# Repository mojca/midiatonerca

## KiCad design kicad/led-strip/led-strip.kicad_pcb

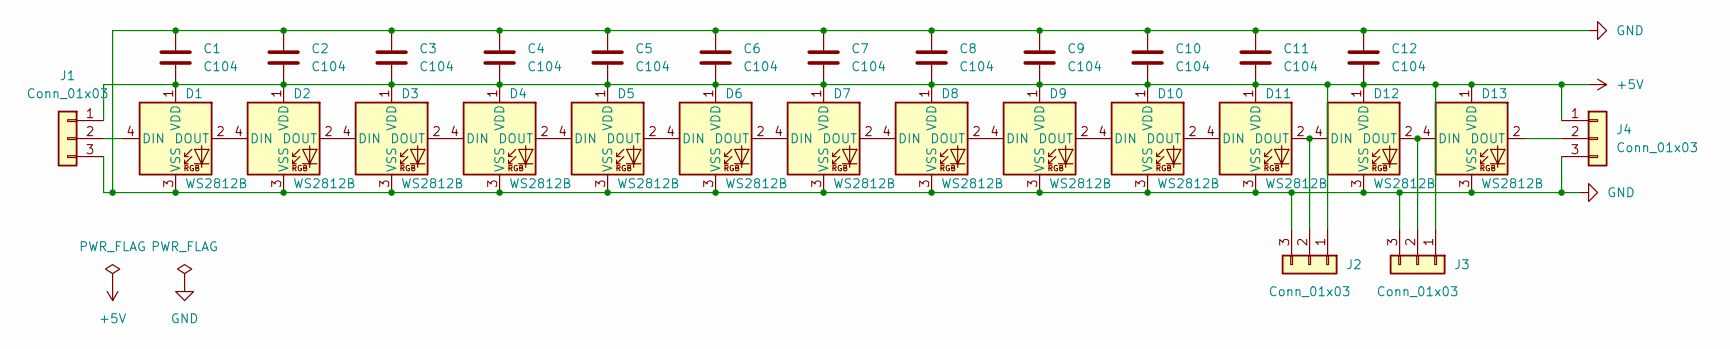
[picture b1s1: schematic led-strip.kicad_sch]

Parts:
C1, C2, C3, C4, C5, C6, C7, C8, C9, C10, C11, C12: C104; C_1206_3216Metric_Pad1.33x1.80mm_HandSolder; LCSC Part # C24497
D1, D2, D3, D4, D5, D6, D7, D8, D9, D10, D11, D12, D13: WS2812B; LED_WS2812B_PLCC4_5.0x5.0mm_P3.2mm; LCSC Part # C2761795
J1, J2, J3, J4: Conn_01x03; SolderWirePad_1x03_SMD_1x3mm

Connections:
+5V: C1.2, C2.2, C3.2, C4.2, C5.2, C6.2, C7.2, C8.2, C9.2, C10.2, C11.2, C12.2, D1.1 (VDD), D2.1 (VDD), D3.1 (VDD), D4.1 (VDD), D5.1 (VDD), D6.1 (VDD), D7.1 (VDD), D8.1 (VDD), D9.1 (VDD), D10.1 (VDD), D11.1 (VDD), D12.1 (VDD), D13.1 (VDD), J1.1, J2.1, J3.1, J4.1
GND: C1.1, C2.1, C3.1, C4.1, C5.1, C6.1, C7.1, C8.1, C9.1, C10.1, C11.1, C12.1, D1.3 (VSS), D2.3 (VSS), D3.3 (VSS), D4.3 (VSS), D5.3 (VSS), D6.3 (VSS), D7.3 (VSS), D8.3 (VSS), D9.3 (VSS), D10.3 (VSS), D11.3 (VSS), D12.3 (VSS), D13.3 (VSS), J1.3, J2.3, J3.3, J4.3
unnamed: D1.2 (DOUT), D2.4 (DIN)
unnamed: D1.4 (DIN), J1.2
unnamed: D2.2 (DOUT), D3.4 (DIN)
unnamed: D3.2 (DOUT), D4.4 (DIN)
unnamed: D4.2 (DOUT), D5.4 (DIN)
unnamed: D5.2 (DOUT), D6.4 (DIN)
unnamed: D6.2 (DOUT), D7.4 (DIN)
unnamed: D7.2 (DOUT), D8.4 (DIN)
unnamed: D8.2 (DOUT), D9.4 (DIN)
unnamed: D10.2 (DOUT), D11.4 (DIN)
unnamed: D9.2 (DOUT), D10.4 (DIN)
unnamed: D11.2 (DOUT), D12.4 (DIN), J2.2
unnamed: D12.2 (DOUT), D13.4 (DIN), J3.2
unnamed: D13.2 (DOUT), J4.2

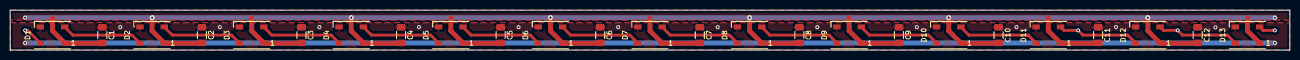
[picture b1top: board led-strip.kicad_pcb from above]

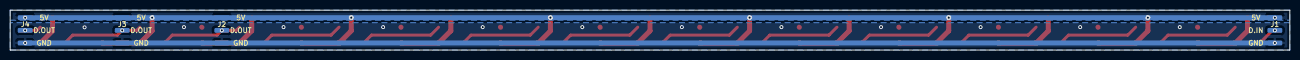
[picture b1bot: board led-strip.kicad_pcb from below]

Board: 2 copper layers, 257.0 x 8.0 mm, 29 parts (4 on the bottom side), 16 nets.

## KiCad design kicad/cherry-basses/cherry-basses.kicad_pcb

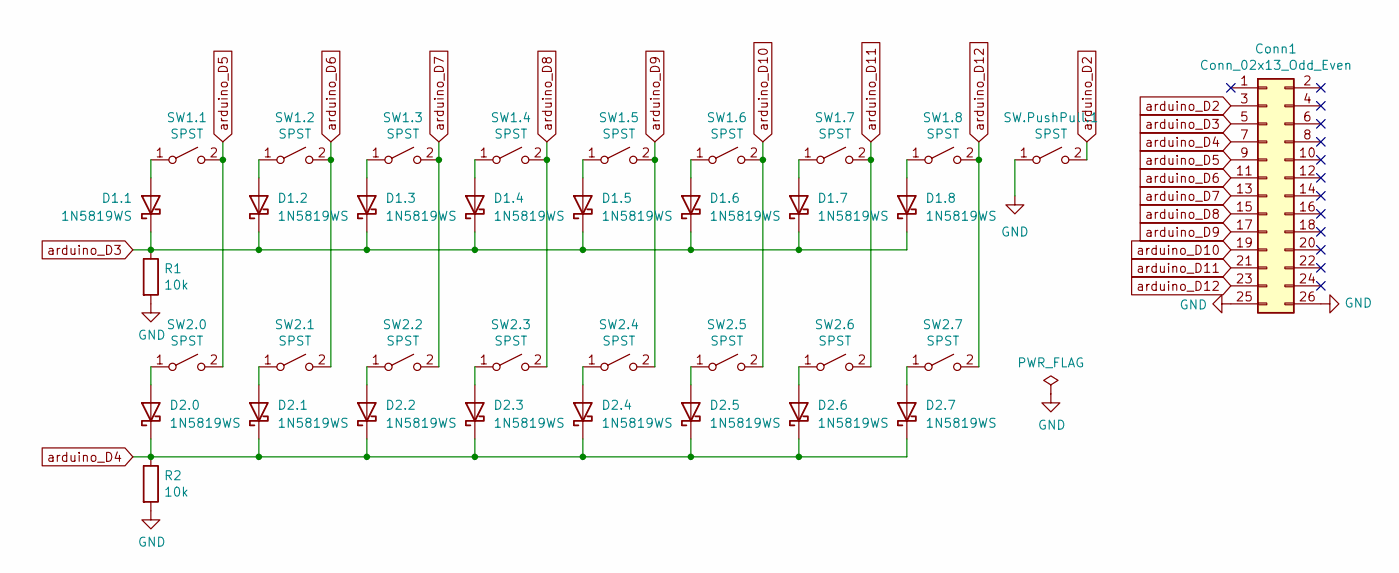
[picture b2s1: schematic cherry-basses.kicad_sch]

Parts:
Conn1: Conn_02x13_Odd_Even; IDC-Header_2x13_P2.54mm_Vertical; LCSC Part # C692426
D1.1, D1.2, D1.3, D1.4, D1.5, D1.6, D1.7, D1.8, D2.0, D2.1, D2.2, D2.3, D2.4, D2.5, D2.6, D2.7: 1N5819WS; D_SOD-323_HandSoldering; LCSC Part # C191023
R1, R2: 10k; R_1206_3216Metric_Pad1.30x1.75mm_HandSolder; LCSC Part # C17902
SW1.1, SW1.2, SW1.3, SW1.4, SW1.5, SW1.6, SW1.7, SW1.8, SW2.0, SW2.1, SW2.2, SW2.3, SW2.4, SW2.5, SW2.6, SW2.7: SPST; SW_Cherry_MX_1.00u_PCB
SW.PushPull.1: SPST; Molex_KK-254_AE-6410-02A_1x02_P2.54mm_Vertical

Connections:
GND: Conn1.25, Conn1.26, R1.2, R2.2, SW.PushPull.1.1 (A)
unnamed: D1.1.2 (A), SW1.1.1 (A)
unnamed: D1.2.2 (A), SW1.2.1 (A)
unnamed: D1.3.2 (A), SW1.3.1 (A)
unnamed: D1.4.2 (A), SW1.4.1 (A)
unnamed: D1.5.2 (A), SW1.5.1 (A)
unnamed: D1.6.2 (A), SW1.6.1 (A)
unnamed: D1.7.2 (A), SW1.7.1 (A)
unnamed: D1.8.2 (A), SW1.8.1 (A)
unnamed: D2.0.2 (A), SW2.0.1 (A)
unnamed: D2.1.2 (A), SW2.1.1 (A)
unnamed: D2.2.2 (A), SW2.2.1 (A)
unnamed: D2.3.2 (A), SW2.3.1 (A)
unnamed: D2.4.2 (A), SW2.4.1 (A)
unnamed: D2.5.2 (A), SW2.5.1 (A)
unnamed: D2.6.2 (A), SW2.6.1 (A)
unnamed: D2.7.2 (A), SW2.7.1 (A)
arduino_D2: Conn1.3, SW.PushPull.1.2 (B)
arduino_D3: Conn1.5, D1.1.1 (K), D1.2.1 (K), D1.3.1 (K), D1.4.1 (K), D1.5.1 (K), D1.6.1 (K), D1.7.1 (K), D1.8.1 (K), R1.1
arduino_D4: Conn1.7, D2.0.1 (K), D2.1.1 (K), D2.2.1 (K), D2.3.1 (K), D2.4.1 (K), D2.5.1 (K), D2.6.1 (K), D2.7.1 (K), R2.1
arduino_D5: Conn1.9, SW1.1.2 (B), SW2.0.2 (B)
arduino_D6: Conn1.11, SW1.2.2 (B), SW2.1.2 (B)
arduino_D7: Conn1.13, SW1.3.2 (B), SW2.2.2 (B)
arduino_D8: Conn1.15, SW1.4.2 (B), SW2.3.2 (B)
arduino_D9: Conn1.17, SW1.5.2 (B), SW2.4.2 (B)
arduino_D10: Conn1.19, SW1.6.2 (B), SW2.5.2 (B)
arduino_D11: Conn1.21, SW1.7.2 (B), SW2.6.2 (B)
arduino_D12: Conn1.23, SW1.8.2 (B), SW2.7.2 (B)

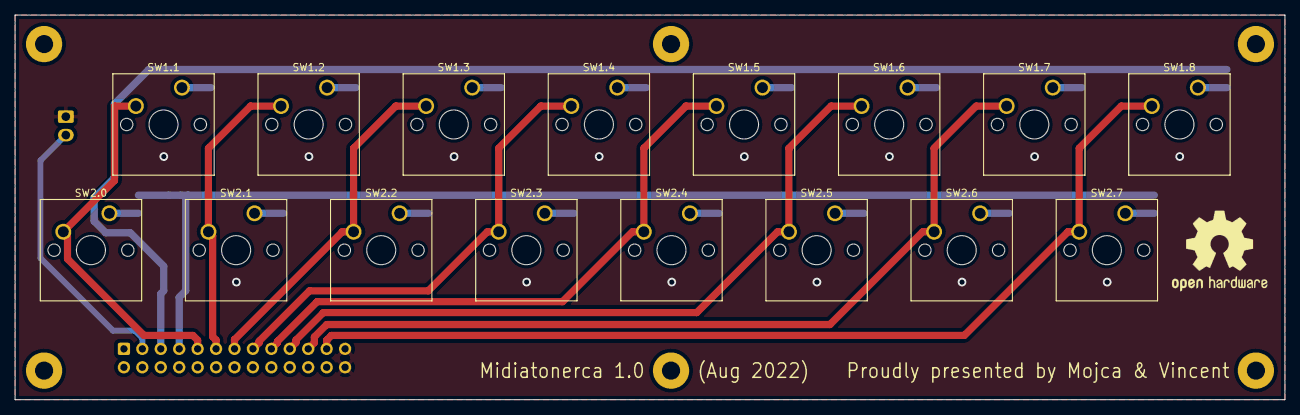
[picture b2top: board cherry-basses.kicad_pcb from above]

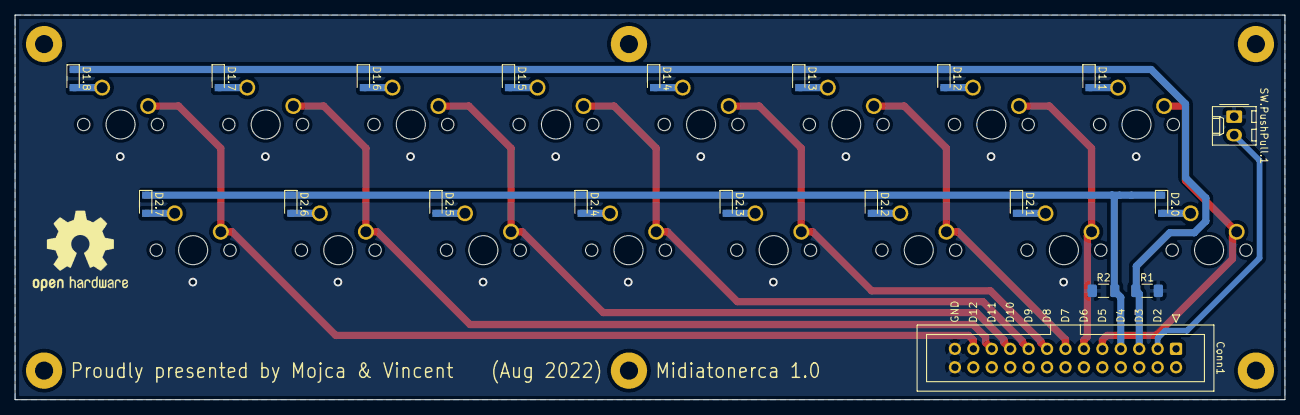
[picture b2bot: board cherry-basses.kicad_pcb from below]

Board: 2 copper layers, 175.0 x 53.0 mm, 36 parts (20 on the bottom side), 28 nets.

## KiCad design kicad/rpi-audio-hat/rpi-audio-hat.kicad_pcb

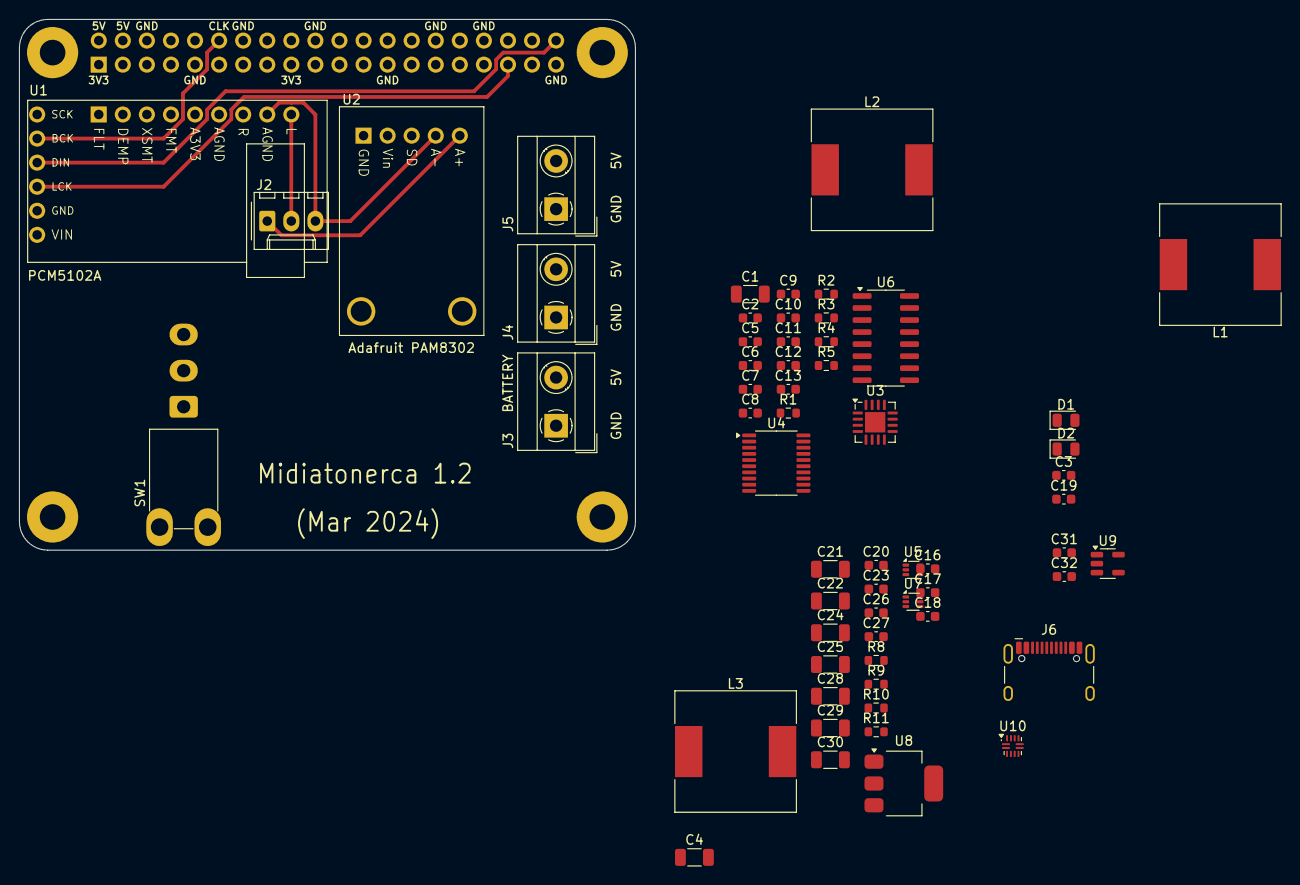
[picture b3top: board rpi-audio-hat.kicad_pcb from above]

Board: 4 copper layers, 65.0 x 56.0 mm, 61 parts (1 on the bottom side), 46 nets.

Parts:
C1, C4, C21, C22, C24, C25, C28, C29, C30: 22uF; C_1206_3216Metric
C2, C3, C6, C7, C9, C13, C19, C20, C26: 100nF; C_0603_1608Metric
C5, C8, C10, C11, C12, C18, C31, C32: 10uF; C_0603_1608Metric
C16, C17: 1uF; C_0603_1608Metric
C23, C27: 22pF; C_0603_1608Metric
D1: Green; LED_0805_2012Metric
D2: Red; LED_0805_2012Metric
J1: Raspberry_Pi_2_3; PinSocket_2x20_P2.54mm_Vertical
J2: Conn_Volume_Slider; Molex_KK-254_AE-6410-03A_1x03_P2.54mm_Vertical
J3, J4, J5: Screw_Terminal_01x02; TerminalBlock_MetzConnect_Type101_RT01602HBWC_1x02_P5.08mm_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
J6: USB_C_Receptacle_USB2.0; USB_C_Receptacle_HCTL_HC-TYPE-C-16P-01A
L1, L2, L3: 3A+ 2.2uH; L_SXN_SMDRI124
R1: 3.9k; R_0603_1608Metric
R2, R3: 220R; R_0603_1608Metric
R4, R5: 100k; R_0603_1608Metric
R8, R10: 220k; R_0603_1608Metric
R9: 30k; R_0603_1608Metric
R11: 22k; R_0603_1608Metric
SW1: SW_SPDT; SW_3P_Mini_Toggle_B068BW_SPDT
U1: PCM5102_breakout
U2: PAM8302A_Adafruit_Board; PAM8302
U3: SLM6800; QFN-16-1EP_4x4mm_P0.65mm_EP2.15x2.15mm
U4: PCM5102A; TSSOP-20_4.4x6.5mm_P0.65mm
U5, U7: TPS563203; SOT-563
U6: PAM8406D; SOP-16_3.9x9.9mm_P1.27mm
U8: TLV76150DCYR; SOT-223-3_TabPin2
U9: LP2985-3.3; SOT-23-5
U10: FUSB303BTMX; Texas_X2QFN-12_1.6x1.6mm_P0.4mm

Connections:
+3.3V: J1.1 (3V3), J1.17 (3V3)
+3.3VA: C5.1, C6.1, C7.1, U4.1 (CPVDD), U4.8 (AVDD), U4.17 (XSMT)
+3V3: C8.1, C9.1, R2.1, R3.1, U4.20 (DVDD)
+5V: C21.1, C23.1, C24.1, J1.2 (5V), J1.4 (5V), J4.2, J5.2, L2.2, R4.1, R8.1, SW1.3 (C), U1.15 (VIN), U2.2 (VDD)
+5VA: C30.1, C31.1, U6.4 (PVDDL), U6.5 (~MUTE), U6.6 (VDD), U6.9 (MODE), U6.12 (~SHND), U6.13 (PVDDR), U8.3 (OUT), U9.1 (VIN), U9.3 (ON/~OFF)
+5VP: J3.2, SW1.2 (B)
+6.6V: C27.1, C28.1, L3.2, R10.1
+VBAT: C22.1, C25.1, U3.9 (BAT), U5.1 (VIN), U5.5 (EN), U7.1 (VIN), U7.5 (EN)
/Battery charger/5VIn: C1.1, C2.1, L1.1, U3.2 (VIN), U3.16 (EN)
/Battery charger/USB-D+: J6.A6 (D+), J6.B6 (D+)
/Battery charger/USB-D-: J6.A7 (D-), J6.B7 (D-)
A+: J2.2, U1.9 (OUTL)
A-: J2.3, U1.8 (AGNDL), U2.4 (IN-)
GND: C1.2, C2.2, C4.2, C5.2, C6.2, C7.2, C8.2, C9.2, C10.2, C12.2, C13.2, C18.2, C19.2, C21.2, C22.2, C24.2, C25.2, C28.2, C29.2, C30.2, C31.2, C32.2, J1.6 (GND), J1.9 (GND), J1.14 (GND), J1.20 (GND), J1.25 (GND), J1.30 (GND), J1.34 (GND), J1.39 (GND), J3.1, J4.1, J5.1, J6.A1 (GND), J6.A12 (GND), J6.B1 (GND), J6.B12 (GND), J6.S1 (SHIELD), R1.2, R5.2, R9.2, R11.2, U1.10 (SCK), U1.14 (GND), U2.1 (GND), U3.4 (PGND), U3.15 (SGND), U3.17 (PGND), U4.3 (CPGND), U4.9 (AGND), U4.10 (DEMP), U4.11 (FLT), U4.16 (FMT), U4.19 (DGND), U5.3 (GND), U6.2 (PGNDL), U6.11 (GND), U6.15 (PGNDR), U7.3 (GND), U8.2 (GND), U9.2 (GND), U10.10 (GND)
unnamed: C3.1, L1.2, U3.5 (LX), U3.6 (LX)
unnamed: C4.1, U3.7 (VSYS), U3.8 (VSYS)
unnamed: D1.2 (A), R2.2
unnamed: D1.1 (K), U3.13 (~CHRG)
unnamed: D2.2 (A), R3.2
unnamed: D2.1 (K), U3.14 (~STBY)
unnamed: J6.A5 (CC1), U10.1 (CC1)
unnamed: J6.B5 (CC2), U10.2 (CC2)
unnamed: C3.2, U3.3 (BST)
unnamed: R1.1, U3.11 (ISET)
unnamed: R4.2, R5.1, U3.1 (NTC)
unnamed: C19.1, U3.12 (TM)
unnamed: C11.2, U4.4 (CAPM)
unnamed: C11.1, U4.2 (CAPP)
unnamed: C12.1, C13.1, U4.18 (LDOO)
unnamed: C10.1, U4.5 (VNEG)
unnamed: C26.2, U5.4 (BST)
unnamed: C27.2, R10.2, R11.1, U5.6 (FB)
unnamed: C26.1, L3.1, U5.2 (SW)
unnamed: C16.2, U6.7 (INL)
unnamed: C17.2, U6.10 (INR)
unnamed: C18.1, U6.8 (VREF)
unnamed: C20.2, U7.4 (BST)
unnamed: C23.2, R8.2, R9.1, U7.6 (FB)
unnamed: C20.1, L2.1, U7.2 (SW)
unnamed: C29.1, U8.1 (IN)
unnamed: C32.1, U9.5 (VOUT)
VUSB: J6.A4 (VBUS), J6.A9 (VBUS), J6.B4 (VBUS), J6.B9 (VBUS), U10.4 (VBUS_DET)
Volume A+: J2.1, U2.5 (IN+)
rpi12: J1.12 (GPIO18/PWM0), U1.11 (BCK), U4.13 (BCK)
rpi35: J1.35 (GPIO19/MISO1), U1.13 (LRCK), U4.12 (SCK), U4.15 (LRCK)
rpi40: J1.40 (GPIO21/SCLK1), U1.12 (DIN), U4.14 (DIN)

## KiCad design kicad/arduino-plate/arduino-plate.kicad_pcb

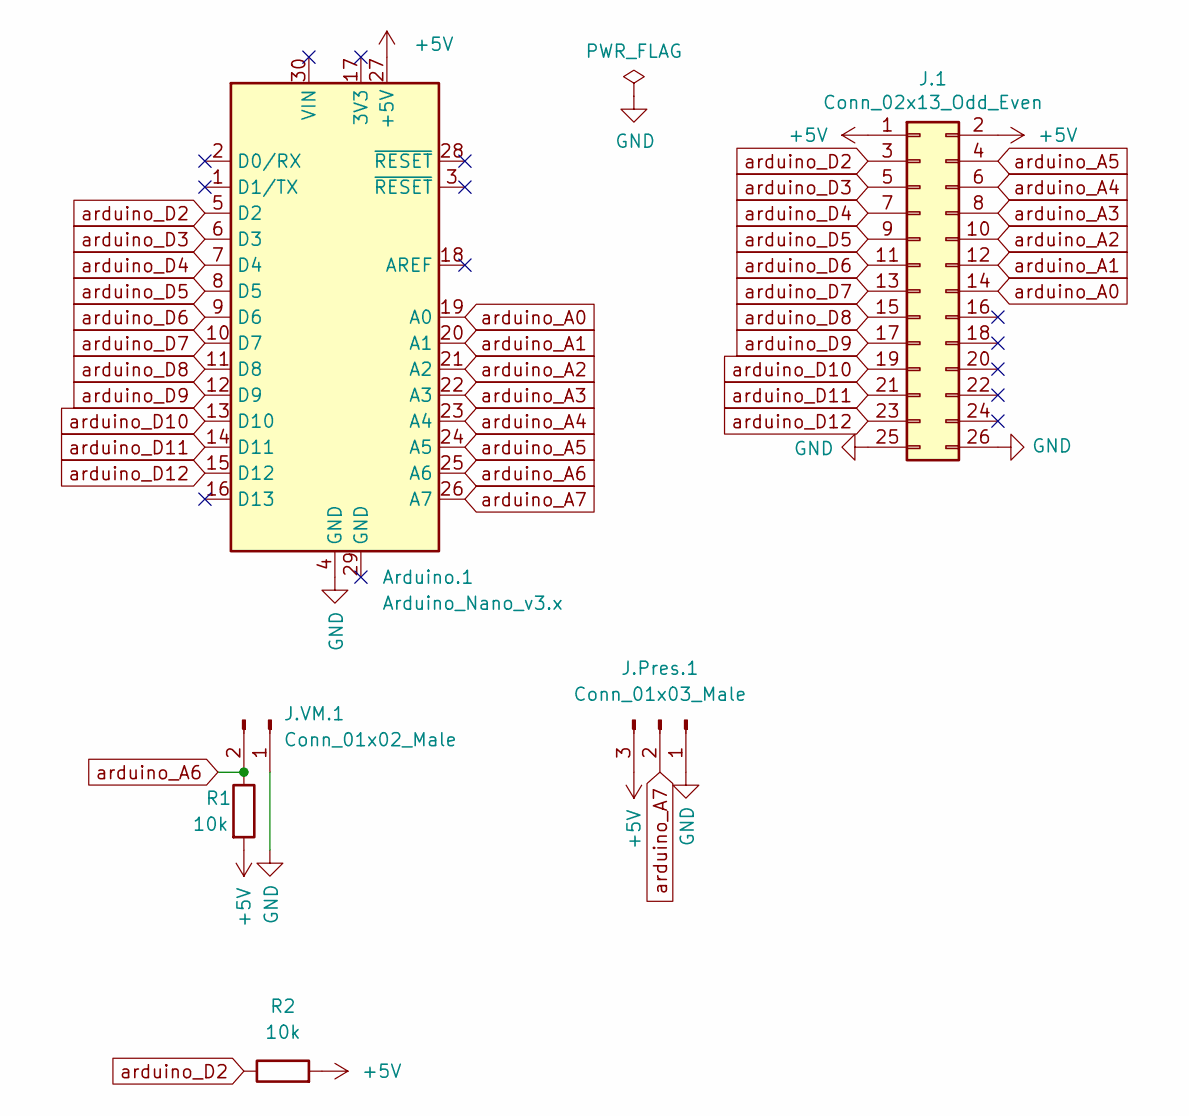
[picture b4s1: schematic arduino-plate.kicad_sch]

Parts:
Arduino.1: Arduino_Nano_v3.x; Arduino_Nano
J.1: Conn_02x13_Odd_Even; IDC-Header_2x13_P2.54mm_Vertical
J.Pres.1: Conn_01x03_Male; Molex_KK-254_AE-6410-03A_1x03_P2.54mm_Vertical
J.VM.1: Conn_01x02_Male; Molex_KK-254_AE-6410-02A_1x02_P2.54mm_Vertical
R1, R2: 10k; R_1206_3216Metric_Pad1.30x1.75mm_HandSolder

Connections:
+5V: Arduino.1.27 (+5V), J.1.1, J.1.2, J.Pres.1.3, R1.2, R2.2
GND: Arduino.1.4 (GND), J.1.25, J.1.26, J.Pres.1.1, J.VM.1.1
arduino_A0: Arduino.1.19 (A0), J.1.14
arduino_A1: Arduino.1.20 (A1), J.1.12
arduino_A2: Arduino.1.21 (A2), J.1.10
arduino_A3: Arduino.1.22 (A3), J.1.8
arduino_A4: Arduino.1.23 (A4), J.1.6
arduino_A5: Arduino.1.24 (A5), J.1.4
arduino_A6: Arduino.1.25 (A6), J.VM.1.2, R1.1
arduino_A7: Arduino.1.26 (A7), J.Pres.1.2
arduino_D2: Arduino.1.5 (D2), J.1.3, R2.1
arduino_D3: Arduino.1.6 (D3), J.1.5
arduino_D4: Arduino.1.7 (D4), J.1.7
arduino_D5: Arduino.1.8 (D5), J.1.9
arduino_D6: Arduino.1.9 (D6), J.1.11
arduino_D7: Arduino.1.10 (D7), J.1.13
arduino_D8: Arduino.1.11 (D8), J.1.15
arduino_D9: Arduino.1.12 (D9), J.1.17
arduino_D10: Arduino.1.13 (D10), J.1.19
arduino_D11: Arduino.1.14 (D11), J.1.21
arduino_D12: Arduino.1.15 (D12), J.1.23

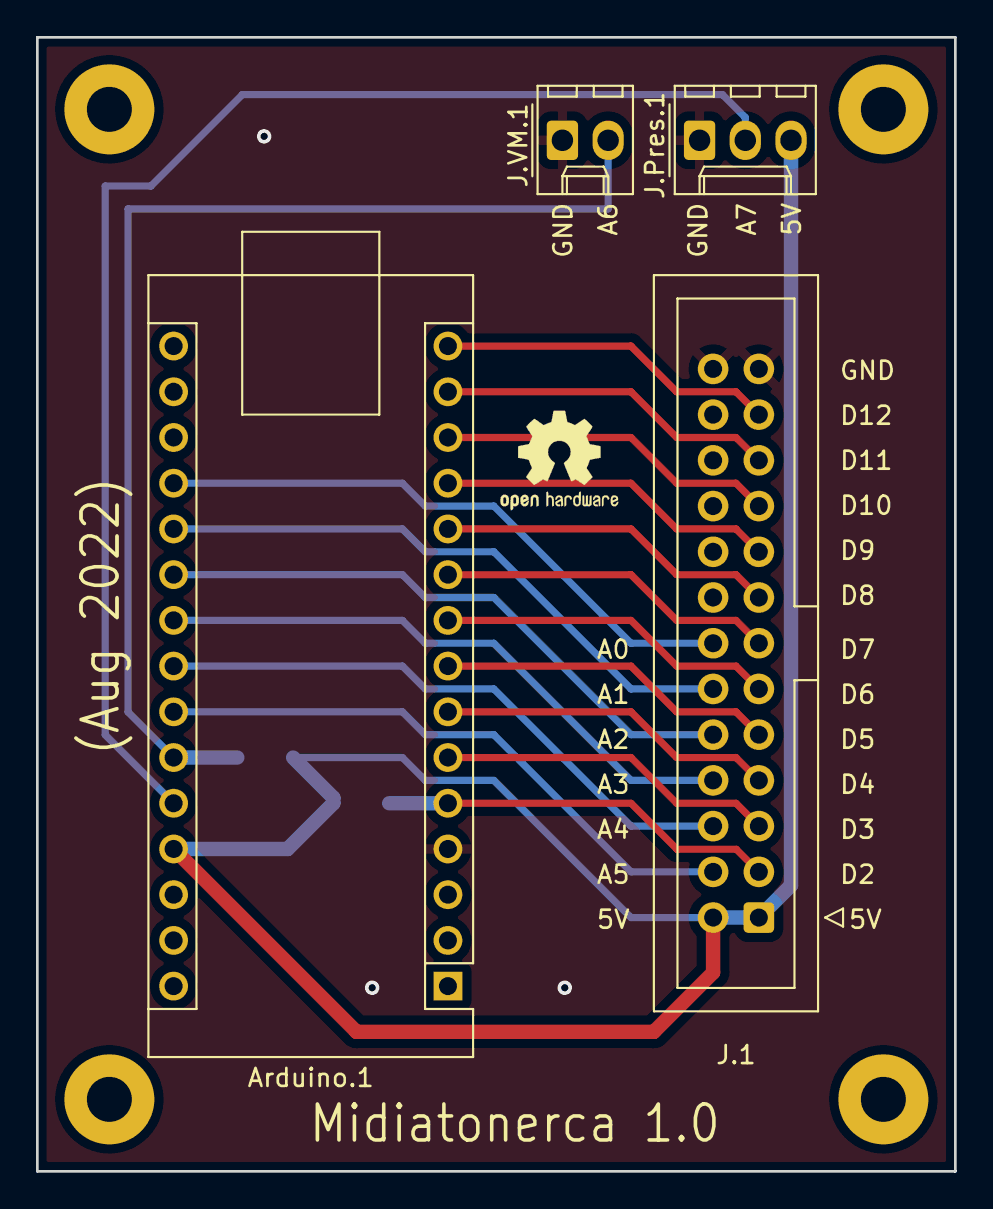
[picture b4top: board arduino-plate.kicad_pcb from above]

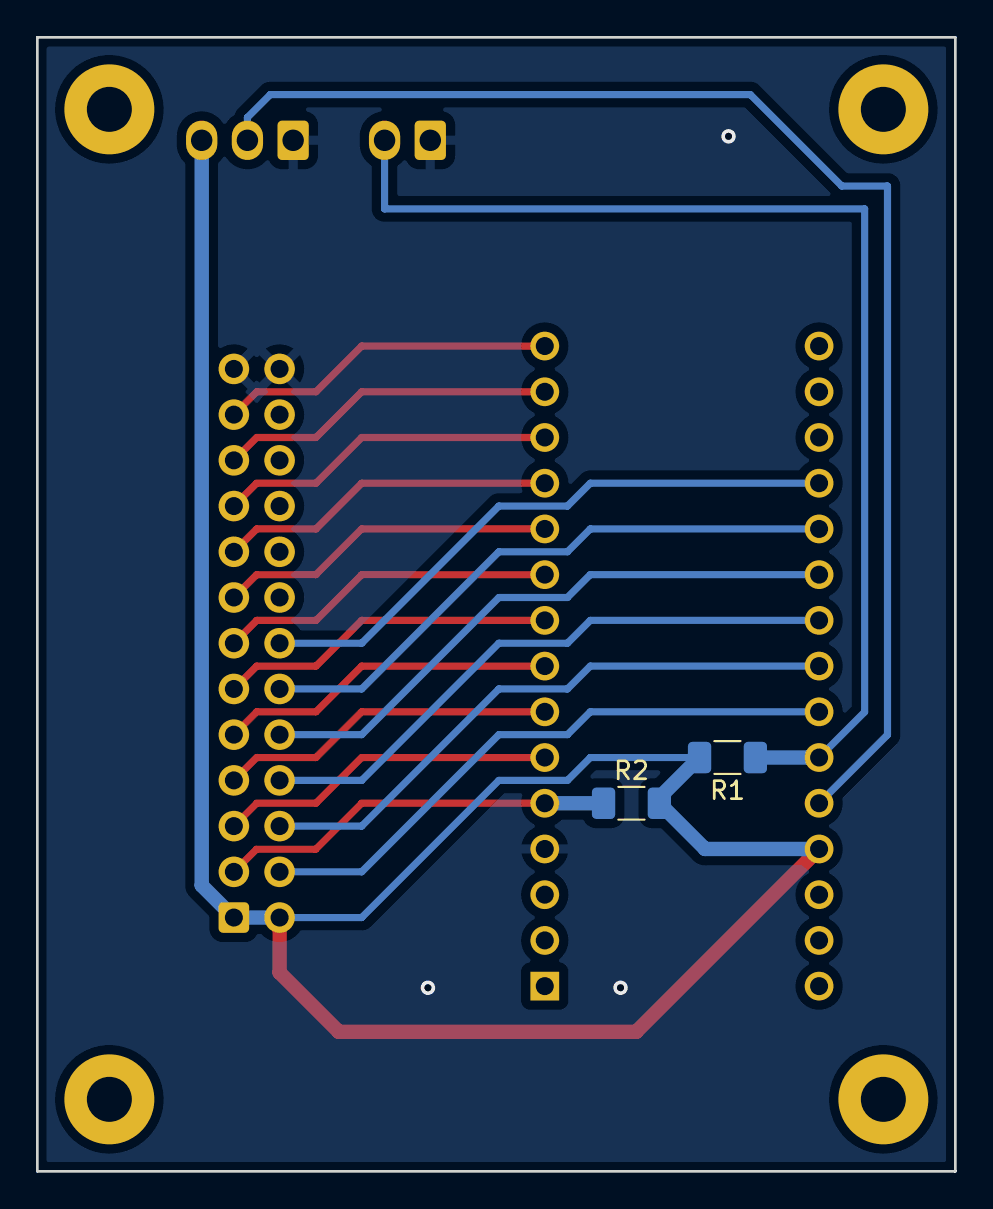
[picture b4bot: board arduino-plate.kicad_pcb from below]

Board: 2 copper layers, 51.0 x 63.0 mm, 6 parts (2 on the bottom side), 21 nets.

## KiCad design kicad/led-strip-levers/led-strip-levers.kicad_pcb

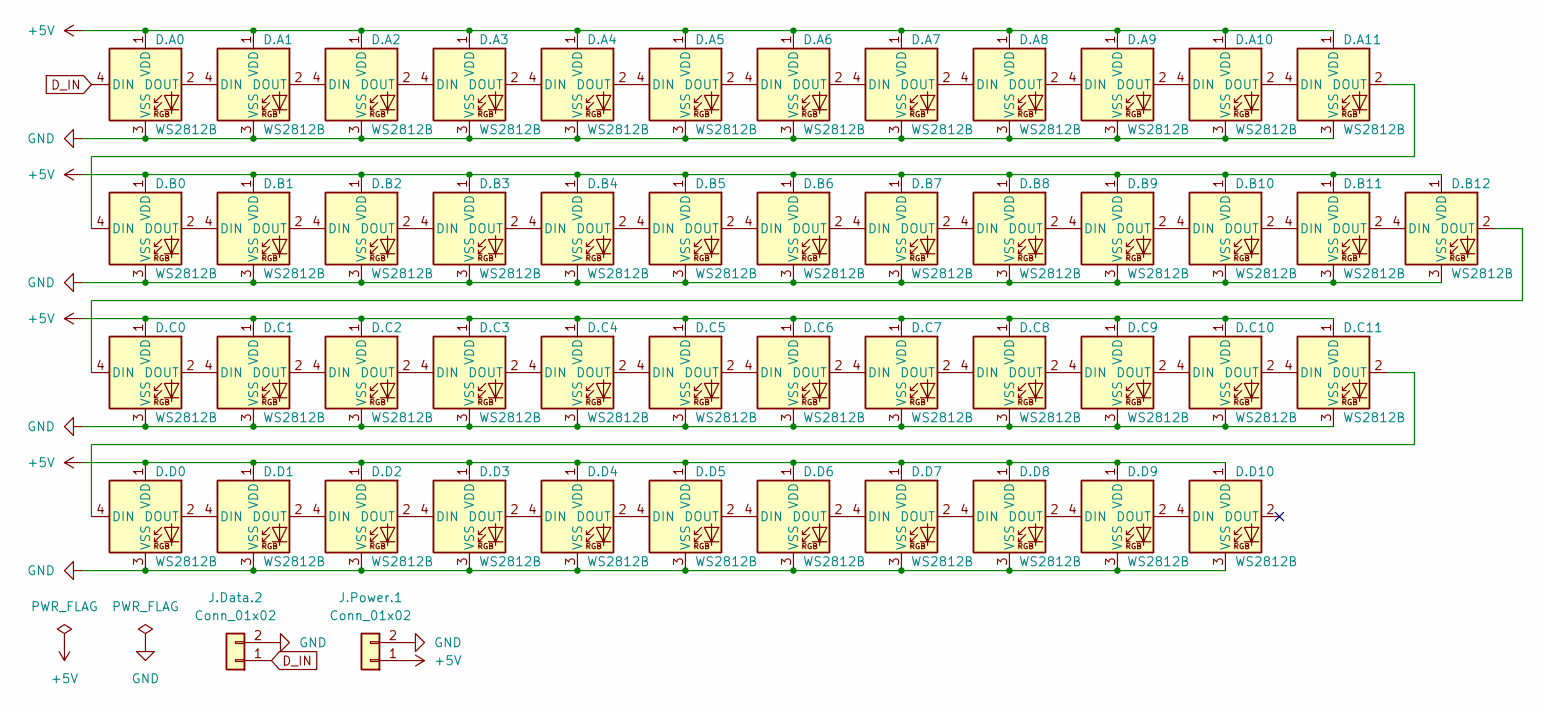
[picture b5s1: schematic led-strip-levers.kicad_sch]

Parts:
D.A0, D.A1, D.A2, D.A3, D.A4, D.A5, D.A6, D.A7, D.A8, D.A9, D.A10, D.A11, D.B0, D.B1, D.B2, D.B3, D.B4, D.B5, D.B6, D.B7, D.B8, D.B9, D.B10, D.B11, D.B12, D.C0, D.C1, D.C2, D.C3, D.C4, D.C5, D.C6, D.C7, D.C8, D.C9, D.C10, D.C11, D.D0, D.D1, D.D2, D.D3, D.D4, D.D5, D.D6, D.D7, D.D8, D.D9, D.D10: WS2812B; LED_WS2812B-Mini_PLCC4_3.5x3.5mm_P1.8mm; LCSC Part # C527089
J.Data.2, J.Power.1: Conn_01x02

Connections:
+5V: D.A0.1 (VDD), D.A1.1 (VDD), D.A2.1 (VDD), D.A3.1 (VDD), D.A4.1 (VDD), D.A5.1 (VDD), D.A6.1 (VDD), D.A7.1 (VDD), D.A8.1 (VDD), D.A9.1 (VDD), D.A10.1 (VDD), D.A11.1 (VDD), D.B0.1 (VDD), D.B1.1 (VDD), D.B2.1 (VDD), D.B3.1 (VDD), D.B4.1 (VDD), D.B5.1 (VDD), D.B6.1 (VDD), D.B7.1 (VDD), D.B8.1 (VDD), D.B9.1 (VDD), D.B10.1 (VDD), D.B11.1 (VDD), D.B12.1 (VDD), D.C0.1 (VDD), D.C1.1 (VDD), D.C2.1 (VDD), D.C3.1 (VDD), D.C4.1 (VDD), D.C5.1 (VDD), D.C6.1 (VDD), D.C7.1 (VDD), D.C8.1 (VDD), D.C9.1 (VDD), D.C10.1 (VDD), D.C11.1 (VDD), D.D0.1 (VDD), D.D1.1 (VDD), D.D2.1 (VDD), D.D3.1 (VDD), D.D4.1 (VDD), D.D5.1 (VDD), D.D6.1 (VDD), D.D7.1 (VDD), D.D8.1 (VDD), D.D9.1 (VDD), D.D10.1 (VDD), J.Power.1.1
D_IN: D.A0.4 (DIN), J.Data.2.1
GND: D.A0.3 (VSS), D.A1.3 (VSS), D.A2.3 (VSS), D.A3.3 (VSS), D.A4.3 (VSS), D.A5.3 (VSS), D.A6.3 (VSS), D.A7.3 (VSS), D.A8.3 (VSS), D.A9.3 (VSS), D.A10.3 (VSS), D.A11.3 (VSS), D.B0.3 (VSS), D.B1.3 (VSS), D.B2.3 (VSS), D.B3.3 (VSS), D.B4.3 (VSS), D.B5.3 (VSS), D.B6.3 (VSS), D.B7.3 (VSS), D.B8.3 (VSS), D.B9.3 (VSS), D.B10.3 (VSS), D.B11.3 (VSS), D.B12.3 (VSS), D.C0.3 (VSS), D.C1.3 (VSS), D.C2.3 (VSS), D.C3.3 (VSS), D.C4.3 (VSS), D.C5.3 (VSS), D.C6.3 (VSS), D.C7.3 (VSS), D.C8.3 (VSS), D.C9.3 (VSS), D.C10.3 (VSS), D.C11.3 (VSS), D.D0.3 (VSS), D.D1.3 (VSS), D.D2.3 (VSS), D.D3.3 (VSS), D.D4.3 (VSS), D.D5.3 (VSS), D.D6.3 (VSS), D.D7.3 (VSS), D.D8.3 (VSS), D.D9.3 (VSS), D.D10.3 (VSS), J.Data.2.2, J.Power.1.2
unnamed: D.A0.2 (DOUT), D.A1.4 (DIN)
unnamed: D.A1.2 (DOUT), D.A2.4 (DIN)
unnamed: D.A2.2 (DOUT), D.A3.4 (DIN)
unnamed: D.A3.2 (DOUT), D.A4.4 (DIN)
unnamed: D.A4.2 (DOUT), D.A5.4 (DIN)
unnamed: D.A5.2 (DOUT), D.A6.4 (DIN)
unnamed: D.A6.2 (DOUT), D.A7.4 (DIN)
unnamed: D.A7.2 (DOUT), D.A8.4 (DIN)
unnamed: D.A8.2 (DOUT), D.A9.4 (DIN)
unnamed: D.A9.2 (DOUT), D.A10.4 (DIN)
unnamed: D.A10.2 (DOUT), D.A11.4 (DIN)
unnamed: D.B0.2 (DOUT), D.B1.4 (DIN)
unnamed: D.A11.2 (DOUT), D.B0.4 (DIN)
unnamed: D.B1.2 (DOUT), D.B2.4 (DIN)
unnamed: D.B2.2 (DOUT), D.B3.4 (DIN)
unnamed: D.B3.2 (DOUT), D.B4.4 (DIN)
unnamed: D.B4.2 (DOUT), D.B5.4 (DIN)
unnamed: D.B5.2 (DOUT), D.B6.4 (DIN)
unnamed: D.B6.2 (DOUT), D.B7.4 (DIN)
unnamed: D.B7.2 (DOUT), D.B8.4 (DIN)
unnamed: D.B8.2 (DOUT), D.B9.4 (DIN)
unnamed: D.B9.2 (DOUT), D.B10.4 (DIN)
unnamed: D.B10.2 (DOUT), D.B11.4 (DIN)
unnamed: D.B11.2 (DOUT), D.B12.4 (DIN)
unnamed: D.C0.2 (DOUT), D.C1.4 (DIN)
unnamed: D.B12.2 (DOUT), D.C0.4 (DIN)
unnamed: D.C1.2 (DOUT), D.C2.4 (DIN)
unnamed: D.C2.2 (DOUT), D.C3.4 (DIN)
unnamed: D.C3.2 (DOUT), D.C4.4 (DIN)
unnamed: D.C4.2 (DOUT), D.C5.4 (DIN)
unnamed: D.C5.2 (DOUT), D.C6.4 (DIN)
unnamed: D.C6.2 (DOUT), D.C7.4 (DIN)
unnamed: D.C7.2 (DOUT), D.C8.4 (DIN)
unnamed: D.C8.2 (DOUT), D.C9.4 (DIN)
unnamed: D.C9.2 (DOUT), D.C10.4 (DIN)
unnamed: D.C10.2 (DOUT), D.C11.4 (DIN)
unnamed: D.D0.2 (DOUT), D.D1.4 (DIN)
unnamed: D.C11.2 (DOUT), D.D0.4 (DIN)
unnamed: D.D1.2 (DOUT), D.D2.4 (DIN)
unnamed: D.D2.2 (DOUT), D.D3.4 (DIN)
unnamed: D.D3.2 (DOUT), D.D4.4 (DIN)
unnamed: D.D4.2 (DOUT), D.D5.4 (DIN)
unnamed: D.D5.2 (DOUT), D.D6.4 (DIN)
unnamed: D.D6.2 (DOUT), D.D7.4 (DIN)
unnamed: D.D7.2 (DOUT), D.D8.4 (DIN)
unnamed: D.D8.2 (DOUT), D.D9.4 (DIN)
unnamed: D.D9.2 (DOUT), D.D10.4 (DIN)

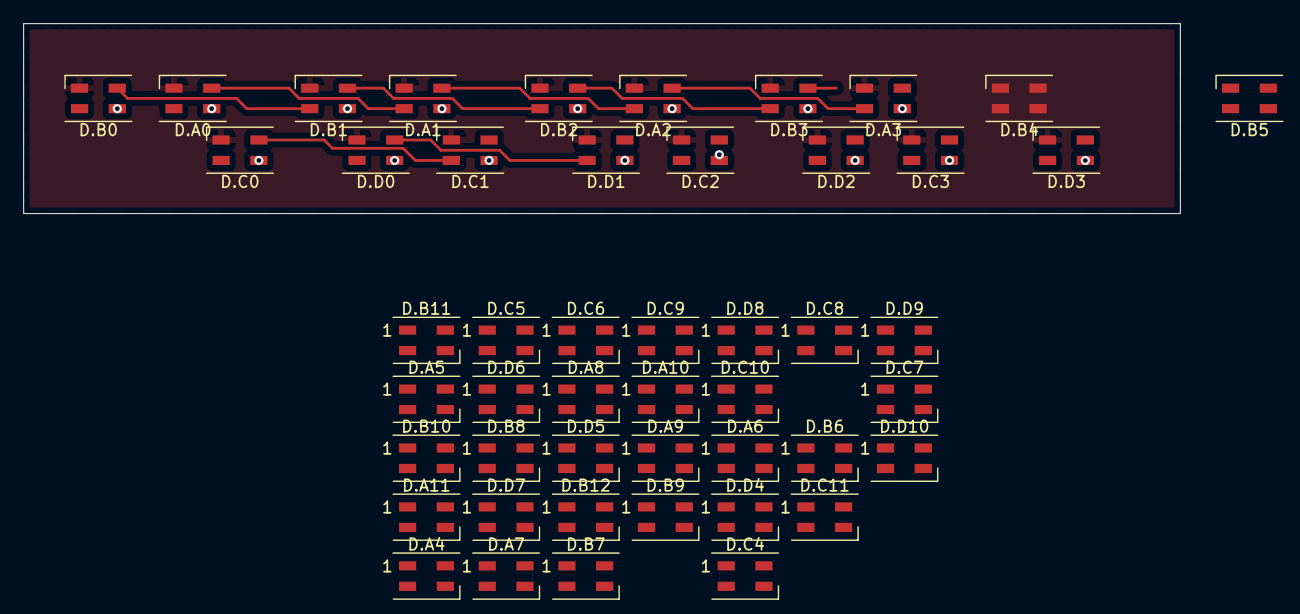
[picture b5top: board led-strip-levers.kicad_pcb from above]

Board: 2 copper layers, 100.5 x 16.5 mm, 48 parts (0 on the bottom side), 49 nets.

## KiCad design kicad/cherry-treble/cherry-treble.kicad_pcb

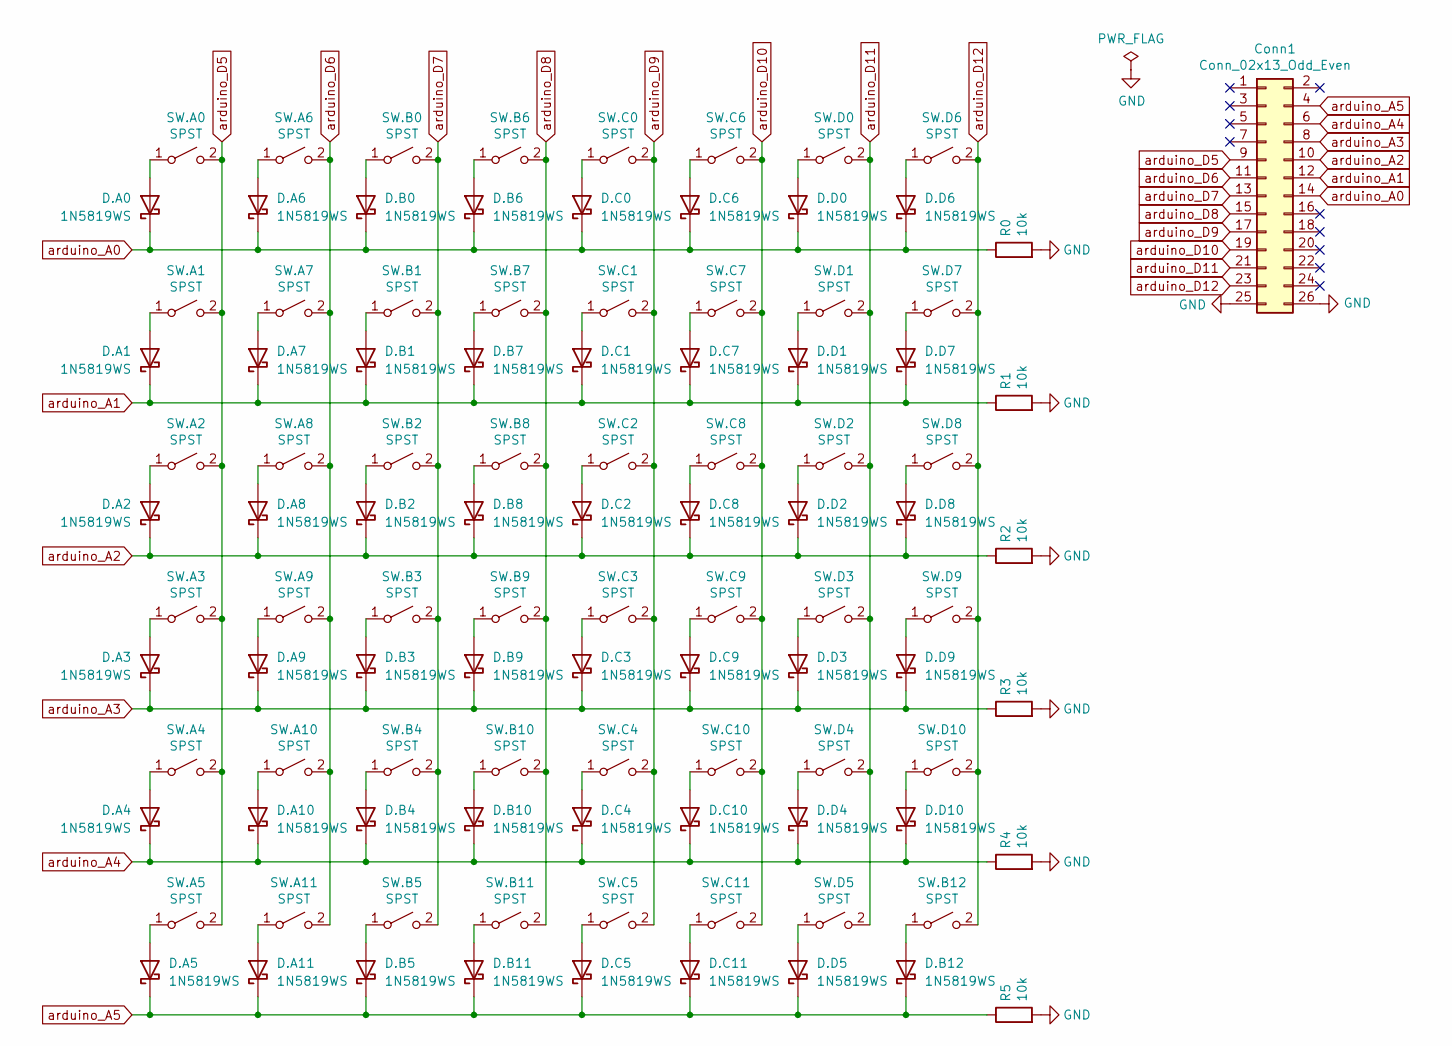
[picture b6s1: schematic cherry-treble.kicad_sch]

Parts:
Conn1: Conn_02x13_Odd_Even; IDC-Header_2x13_P2.54mm_Vertical
D.A0, D.A1, D.A2, D.A3, D.A4, D.A5, D.A6, D.A7, D.A8, D.A9, D.A10, D.A11, D.B0, D.B1, D.B2, D.B3, D.B4, D.B5, D.B6, D.B7, D.B8, D.B9, D.B10, D.B11, D.B12, D.C0, D.C1, D.C2, D.C3, D.C4, D.C5, D.C6, D.C7, D.C8, D.C9, D.C10, D.C11, D.D0, D.D1, D.D2, D.D3, D.D4, D.D5, D.D6, D.D7, D.D8, D.D9, D.D10: 1N5819WS; D_SOD-323_HandSoldering; LCSC Part # C2128
R0, R1, R2, R3, R4, R5: 10k; R_1206_3216Metric_Pad1.30x1.75mm_HandSolder; LCSC Part # C17902
SW.A0, SW.A1, SW.A2, SW.A3, SW.A4, SW.A5, SW.A6, SW.A7, SW.A8, SW.A9, SW.A10, SW.A11, SW.B0, SW.B1, SW.B2, SW.B3, SW.B4, SW.B5, SW.B6, SW.B7, SW.B8, SW.B9, SW.B10, SW.B11, SW.B12, SW.C0, SW.C1, SW.C2, SW.C3, SW.C4, SW.C5, SW.C6, SW.C7, SW.C8, SW.C9, SW.C10, SW.C11, SW.D0, SW.D1, SW.D2, SW.D3, SW.D4, SW.D5, SW.D6, SW.D7, SW.D8, SW.D9, SW.D10: SPST; SW_Cherry_MX_1.00u_PCB

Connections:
GND: Conn1.25, Conn1.26, R0.2, R1.2, R2.2, R3.2, R4.2, R5.2
unnamed: D.A0.2 (A), SW.A0.1 (A)
unnamed: D.A1.2 (A), SW.A1.1 (A)
unnamed: D.A2.2 (A), SW.A2.1 (A)
unnamed: D.A3.2 (A), SW.A3.1 (A)
unnamed: D.A4.2 (A), SW.A4.1 (A)
unnamed: D.A5.2 (A), SW.A5.1 (A)
unnamed: D.A6.2 (A), SW.A6.1 (A)
unnamed: D.A7.2 (A), SW.A7.1 (A)
unnamed: D.A8.2 (A), SW.A8.1 (A)
unnamed: D.A9.2 (A), SW.A9.1 (A)
unnamed: D.A10.2 (A), SW.A10.1 (A)
unnamed: D.A11.2 (A), SW.A11.1 (A)
unnamed: D.B0.2 (A), SW.B0.1 (A)
unnamed: D.B1.2 (A), SW.B1.1 (A)
unnamed: D.B2.2 (A), SW.B2.1 (A)
unnamed: D.B3.2 (A), SW.B3.1 (A)
unnamed: D.B4.2 (A), SW.B4.1 (A)
unnamed: D.B5.2 (A), SW.B5.1 (A)
unnamed: D.B6.2 (A), SW.B6.1 (A)
unnamed: D.B7.2 (A), SW.B7.1 (A)
unnamed: D.B8.2 (A), SW.B8.1 (A)
unnamed: D.B9.2 (A), SW.B9.1 (A)
unnamed: D.B10.2 (A), SW.B10.1 (A)
unnamed: D.B11.2 (A), SW.B11.1 (A)
unnamed: D.B12.2 (A), SW.B12.1 (A)
unnamed: D.C0.2 (A), SW.C0.1 (A)
unnamed: D.C1.2 (A), SW.C1.1 (A)
unnamed: D.C2.2 (A), SW.C2.1 (A)
unnamed: D.C3.2 (A), SW.C3.1 (A)
unnamed: D.C4.2 (A), SW.C4.1 (A)
unnamed: D.C5.2 (A), SW.C5.1 (A)
unnamed: D.C6.2 (A), SW.C6.1 (A)
unnamed: D.C7.2 (A), SW.C7.1 (A)
unnamed: D.C8.2 (A), SW.C8.1 (A)
unnamed: D.C9.2 (A), SW.C9.1 (A)
unnamed: D.C10.2 (A), SW.C10.1 (A)
unnamed: D.C11.2 (A), SW.C11.1 (A)
unnamed: D.D0.2 (A), SW.D0.1 (A)
unnamed: D.D1.2 (A), SW.D1.1 (A)
unnamed: D.D2.2 (A), SW.D2.1 (A)
unnamed: D.D3.2 (A), SW.D3.1 (A)
unnamed: D.D4.2 (A), SW.D4.1 (A)
unnamed: D.D5.2 (A), SW.D5.1 (A)
unnamed: D.D6.2 (A), SW.D6.1 (A)
unnamed: D.D7.2 (A), SW.D7.1 (A)
unnamed: D.D8.2 (A), SW.D8.1 (A)
unnamed: D.D9.2 (A), SW.D9.1 (A)
unnamed: D.D10.2 (A), SW.D10.1 (A)
arduino_A0: Conn1.14, D.A0.1 (K), D.A6.1 (K), D.B0.1 (K), D.B6.1 (K), D.C0.1 (K), D.C6.1 (K), D.D0.1 (K), D.D6.1 (K), R0.1
arduino_A1: Conn1.12, D.A1.1 (K), D.A7.1 (K), D.B1.1 (K), D.B7.1 (K), D.C1.1 (K), D.C7.1 (K), D.D1.1 (K), D.D7.1 (K), R1.1
arduino_A2: Conn1.10, D.A2.1 (K), D.A8.1 (K), D.B2.1 (K), D.B8.1 (K), D.C2.1 (K), D.C8.1 (K), D.D2.1 (K), D.D8.1 (K), R2.1
arduino_A3: Conn1.8, D.A3.1 (K), D.A9.1 (K), D.B3.1 (K), D.B9.1 (K), D.C3.1 (K), D.C9.1 (K), D.D3.1 (K), D.D9.1 (K), R3.1
arduino_A4: Conn1.6, D.A4.1 (K), D.A10.1 (K), D.B4.1 (K), D.B10.1 (K), D.C4.1 (K), D.C10.1 (K), D.D4.1 (K), D.D10.1 (K), R4.1
arduino_A5: Conn1.4, D.A5.1 (K), D.A11.1 (K), D.B5.1 (K), D.B11.1 (K), D.B12.1 (K), D.C5.1 (K), D.C11.1 (K), D.D5.1 (K), R5.1
arduino_D5: Conn1.9, SW.A0.2 (B), SW.A1.2 (B), SW.A2.2 (B), SW.A3.2 (B), SW.A4.2 (B), SW.A5.2 (B)
arduino_D6: Conn1.11, SW.A6.2 (B), SW.A7.2 (B), SW.A8.2 (B), SW.A9.2 (B), SW.A10.2 (B), SW.A11.2 (B)
arduino_D7: Conn1.13, SW.B0.2 (B), SW.B1.2 (B), SW.B2.2 (B), SW.B3.2 (B), SW.B4.2 (B), SW.B5.2 (B)
arduino_D8: Conn1.15, SW.B6.2 (B), SW.B7.2 (B), SW.B8.2 (B), SW.B9.2 (B), SW.B10.2 (B), SW.B11.2 (B)
arduino_D9: Conn1.17, SW.C0.2 (B), SW.C1.2 (B), SW.C2.2 (B), SW.C3.2 (B), SW.C4.2 (B), SW.C5.2 (B)
arduino_D10: Conn1.19, SW.C6.2 (B), SW.C7.2 (B), SW.C8.2 (B), SW.C9.2 (B), SW.C10.2 (B), SW.C11.2 (B)
arduino_D11: Conn1.21, SW.D0.2 (B), SW.D1.2 (B), SW.D2.2 (B), SW.D3.2 (B), SW.D4.2 (B), SW.D5.2 (B)
arduino_D12: Conn1.23, SW.B12.2 (B), SW.D6.2 (B), SW.D7.2 (B), SW.D8.2 (B), SW.D9.2 (B), SW.D10.2 (B)

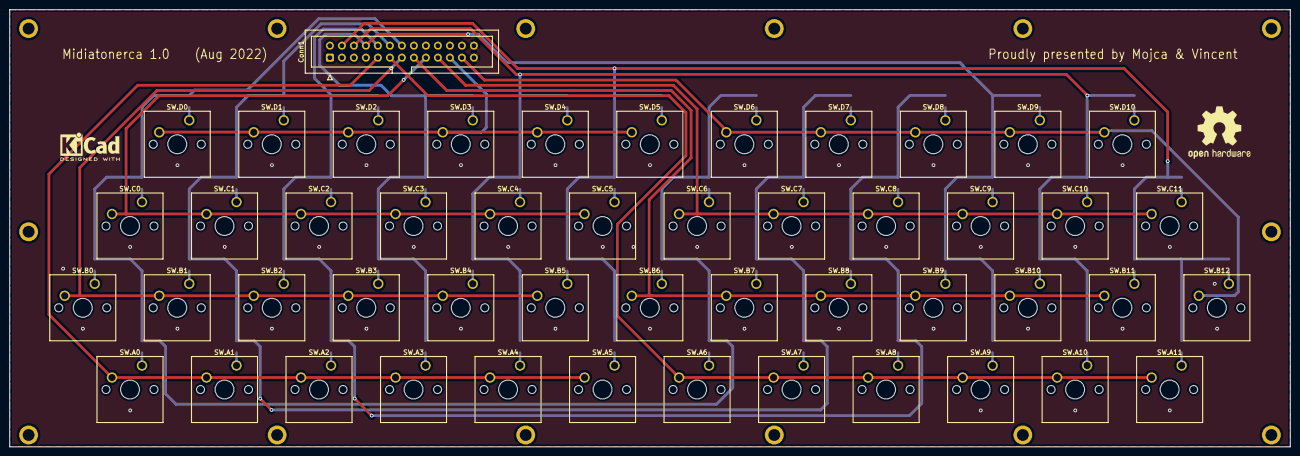
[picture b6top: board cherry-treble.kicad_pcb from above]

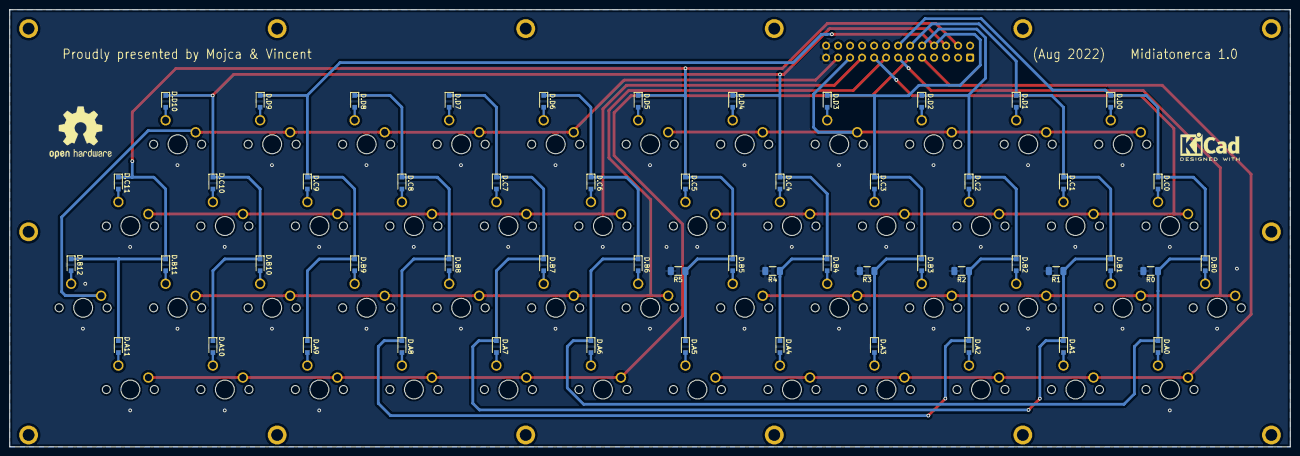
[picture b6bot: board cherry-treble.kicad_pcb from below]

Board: 2 copper layers, 271.0 x 92.5 mm, 103 parts (54 on the bottom side), 63 nets.
